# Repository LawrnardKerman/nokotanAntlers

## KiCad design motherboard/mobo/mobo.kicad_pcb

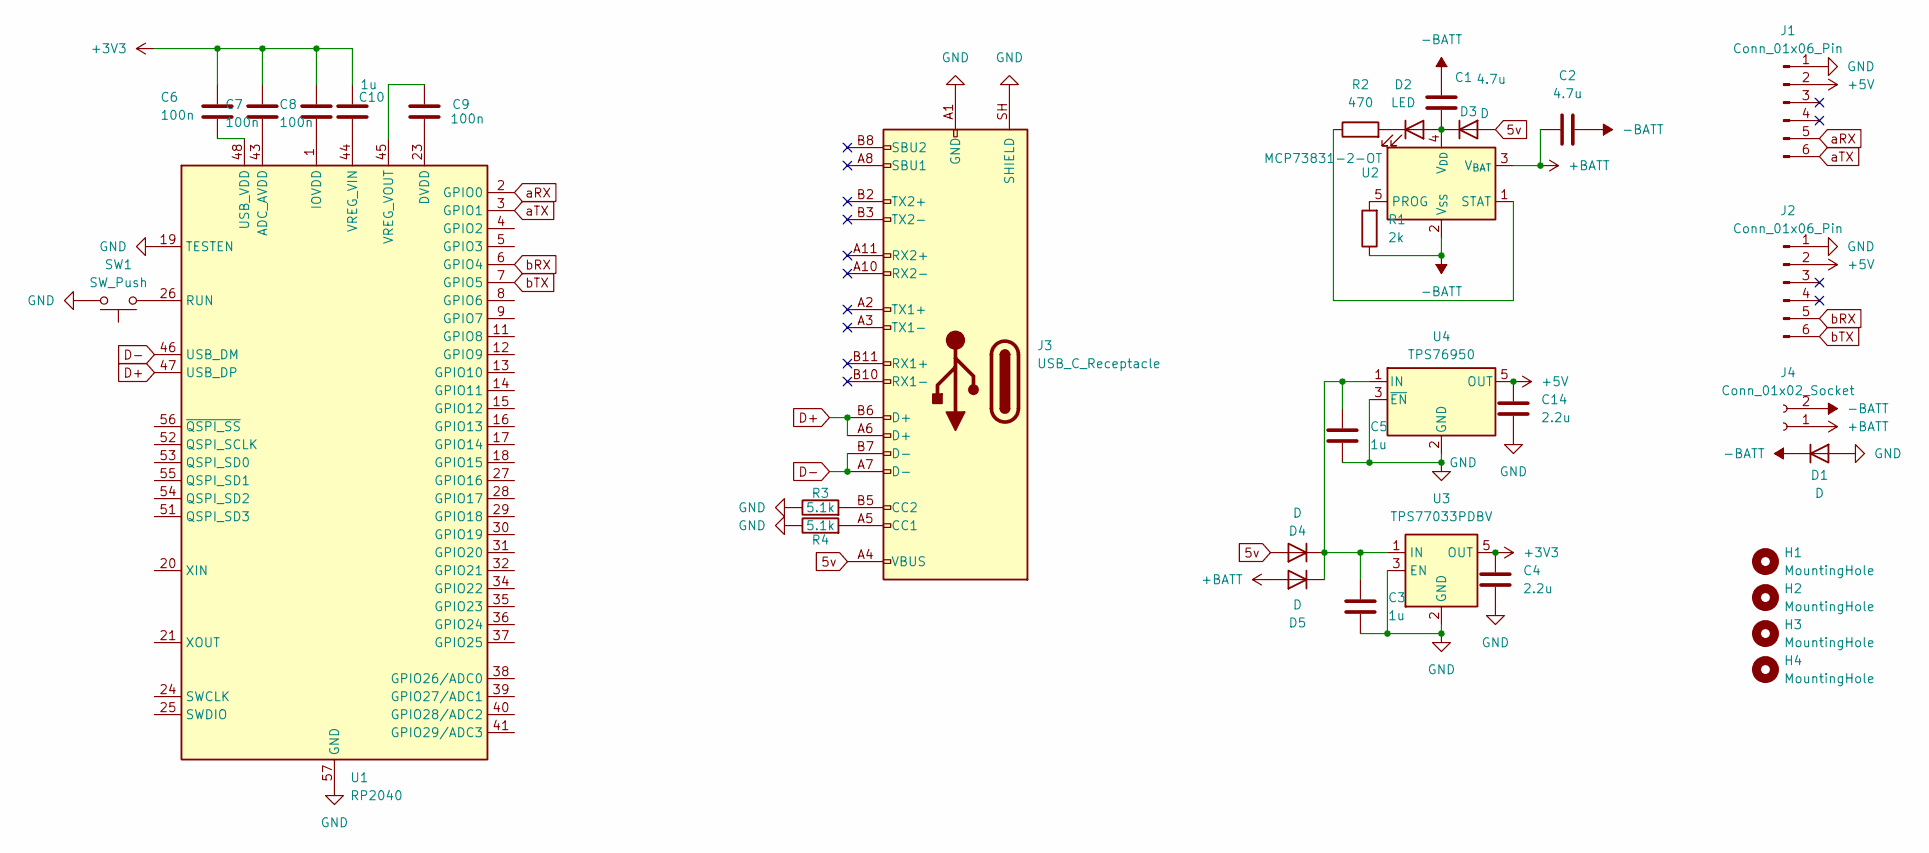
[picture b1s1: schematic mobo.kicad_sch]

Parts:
C1, C2: 4.7u; C_0201_0603Metric_Pad0.64x0.40mm_HandSolder
C3, C5, C10: 1u; C_0201_0603Metric_Pad0.64x0.40mm_HandSolder
C4, C14: 2.2u; C_0201_0603Metric_Pad0.64x0.40mm_HandSolder
C6, C7, C8, C9: 100n; C_0201_0603Metric_Pad0.64x0.40mm_HandSolder
D1, D3, D4, D5: D; D_0201_0603Metric_Pad0.64x0.40mm_HandSolder
D2: LED; LED_0201_0603Metric_Pad0.64x0.40mm_HandSolder
H1, H2, H3, H4: MountingHole; MountingHole_3.2mm_M3
J1, J2: Conn_01x06_Pin; PinHeader_1x06_P2.00mm_Vertical
J3: USB_C_Receptacle; USB_C_Receptacle_Amphenol_12401548E4-2A
J4: Conn_01x02_Socket; JST_PH_B2B-PH-K_1x02_P2.00mm_Vertical
R1: 2k; R_0201_0603Metric_Pad0.64x0.40mm_HandSolder
R2: 470; R_0201_0603Metric_Pad0.64x0.40mm_HandSolder
R3, R4: 5.1k; R_0201_0603Metric
SW1: SW_Push; SW_Push_1P1T_NO_CK_KMR2
U1: RP2040; QFN-56-1EP_7x7mm_P0.4mm_EP3.2x3.2mm
U2: MCP73831-2-OT; SOT-23-5
U3: TPS77033PDBV; SOT-23-5
U4: TPS76950; SOT-23-5

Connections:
5v: D3.2 (A), D4.2 (A), J3.A4 (VBUS), J3.A9 (VBUS), J3.B4 (VBUS), J3.B9 (VBUS)
+3V3: C4.1, C6.1, C7.1, C8.1, C10.1, U3.5 (OUT)
+5V: C14.1, J1.2, J2.2, U4.5 (OUT)
+BATT: C2.1, D5.2 (A), J4.1, U2.3 (V_{BAT})
-BATT: C1.1, C2.2, D1.1 (K), J4.2, R1.1, U2.2 (V_{SS})
D+: J3.A6 (D+), J3.B6 (D+), U1.47 (USB_DP)
D-: J3.A7 (D-), J3.B7 (D-), U1.46 (USB_DM)
GND: C3.2, C4.2, C5.2, C14.2, D1.2 (A), J1.1, J2.1, J3.A1 (GND), J3.A12 (GND), J3.B1 (GND), J3.B12 (GND), J3.SH (SHIELD), R3.1, R4.1, SW1.2, U1.19 (TESTEN), U1.57 (GND), U3.2 (GND), U3.3 (EN), U4.2 (GND), U4.3 (~EN)
unnamed: C8.2, U1.1 (IOVDD), U1.10 (IOVDD), U1.22 (IOVDD), U1.33 (IOVDD), U1.42 (IOVDD), U1.49 (IOVDD)
unnamed: C9.2, U1.23 (DVDD), U1.50 (DVDD)
unnamed: C1.2, D2.2 (A), D3.1 (K), U2.4 (V_{DD})
unnamed: D2.1 (K), R2.2
unnamed: C3.1, C5.1, D4.1 (K), D5.1 (K), U3.1 (IN), U4.1 (IN)
unnamed: J3.A5 (CC1), R4.2
unnamed: J3.B5 (CC2), R3.2
unnamed: C7.2, U1.43 (ADC_AVDD)
unnamed: SW1.1, U1.26 (RUN)
unnamed: C6.2, U1.48 (USB_VDD)
unnamed: C10.2, U1.44 (VREG_VIN)
unnamed: C9.1, U1.45 (VREG_VOUT)
unnamed: R1.2, U2.5 (PROG)
unnamed: R2.1, U2.1 (STAT)
aRX: J1.5, U1.2 (GPIO0)
aTX: J1.6, U1.3 (GPIO1)
bRX: J2.5, U1.6 (GPIO4)
bTX: J2.6, U1.7 (GPIO5)

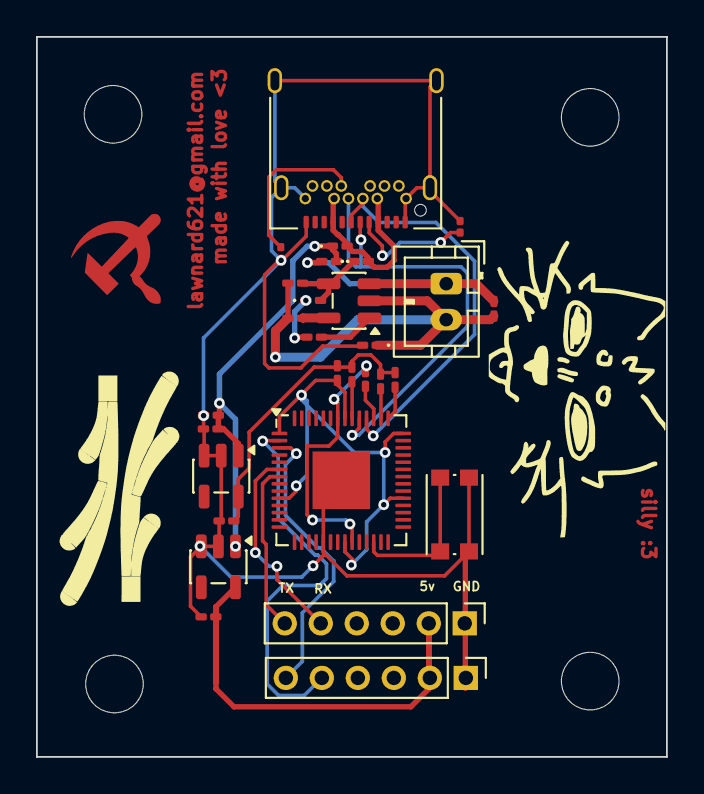
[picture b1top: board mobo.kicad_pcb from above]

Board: 2 copper layers, 35.0 x 40.0 mm, 33 parts (0 on the bottom side), 26 nets.
